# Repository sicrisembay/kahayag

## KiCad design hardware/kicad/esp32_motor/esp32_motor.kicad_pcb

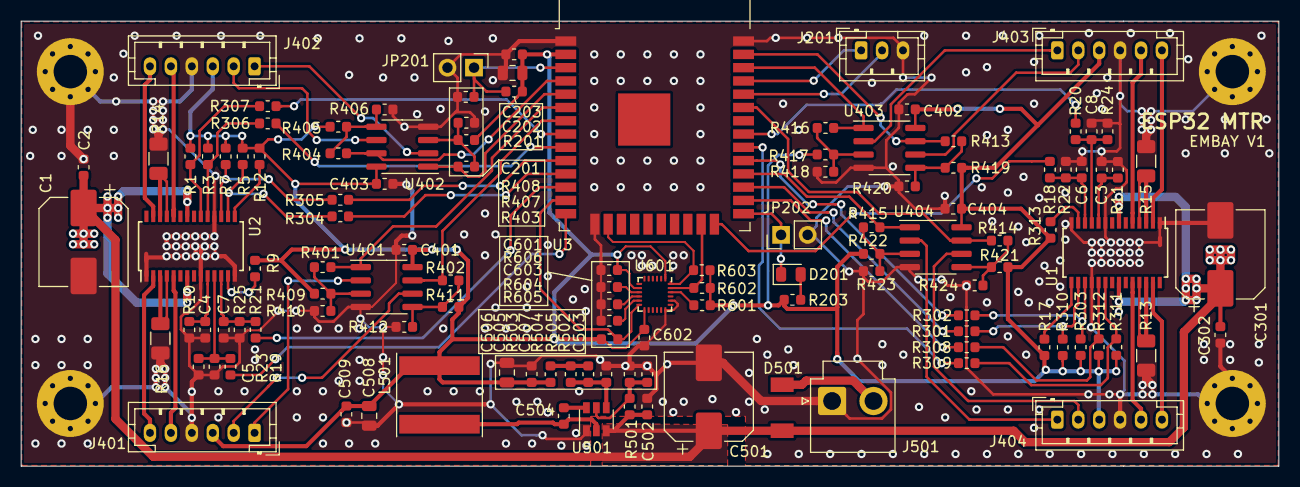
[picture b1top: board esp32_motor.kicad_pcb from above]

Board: 2 copper layers, 120.3 x 42.5 mm, 124 parts (0 on the bottom side), 87 nets.

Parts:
C1, C301, C501: 100uF; CP_Elec_8x10
C2, C5, C6, C7, C8, C201, C203, C302, C401, C402, C403, C404, C504, C505, C509, C602, C603: 0.1uF; C_0603_1608Metric
C3, C4: 470pF; C_0603_1608Metric
C202, C506, C508: 22uF; C_0805_2012Metric
C502: 1uF; C_0603_1608Metric
C503: DNP; C_0603_1608Metric
C507: 75pF; C_0603_1608Metric
C601: 10nF; C_0603_1608Metric
D201: LED; LED_0805_2012Metric
D501: SK14; SOD-128
H701, H702, H703, H704: MountingHole_Pad; MountingHole_3.2mm_M3_Pad_Via
J201: Program; JST_PH_B3B-PH-K_1x03_P2.00mm_Vertical
J401: MOTOR1; JST_PH_B6B-PH-K_1x06_P2.00mm_Vertical
J402: MOTOR2; JST_PH_B6B-PH-K_1x06_P2.00mm_Vertical
J403: MOTOR3; JST_PH_B6B-PH-K_1x06_P2.00mm_Vertical
J404: MOTOR4; JST_PH_B6B-PH-K_1x06_P2.00mm_Vertical
J501: 24V_IN; JST_VH_B2P-VH-B_1x02_P3.96mm_Vertical
JP201: RESET; PinHeader_1x02_P2.54mm_Vertical
JP202: MODE; PinHeader_1x02_P2.54mm_Vertical
L501: 10uH; L_Taiyo-Yuden_NR-80xx
R1, R3, R5, R7, R9, R12, R17, R201, R303, R310, R311, R312, R313, R405, R406, R407, R408, R409, R410, R411, R412, R417, R418, R419, R420, R421, R422, R423, R424, R601, R604, R605, R606: 10K; R_0603_1608Metric
R10, R11: 82K; R_0603_1608Metric
R13, R14, R15, R16: 0.1; R_1206_3216Metric
R18, R19, R20, R21, R602, R603: 4.7K; R_0603_1608Metric
R22, R23, R24, R25: 5K; R_0603_1608Metric
R203: 220R; R_0603_1608Metric
R301, R302, R304, R305, R306, R307, R308, R309: 200; R_0603_1608Metric
R401, R402, R403, R404, R413, R414, R415, R416: 50K; R_0603_1608Metric
R501: 511K; R_0603_1608Metric
R502, R504: 100K; R_0603_1608Metric
R503: 49.9R; R_0603_1608Metric
R505: 22K; R_0603_1608Metric
U1, U2: BD62220AEFV; HTSSOP-28-BD62220AEFV
U3: ESP32-WROOM-32D; ESP32-WROOM-32
U401, U402, U403, U404: LM393; SOIC-8_3.9x4.9mm_P1.27mm
U501: TPS54302; SOT-23-6
U601: MPU-9250; InvenSense_QFN-24_3x3mm_P0.4mm

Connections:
3V3_OUT: C202.1, C203.1, C401.1, C402.1, C403.1, C404.1, C505.2, C506.2, C508.2, C509.2, C601.1, C602.1, J401.3, J402.3, J403.3, J404.3, L501.2, R1.1, R3.1, R5.1, R7.1, R9.1, R12.1, R17.1, R201.1, R203.1, R303.1, R310.1, R311.1, R312.1, R313.1, R405.1, R407.1, R409.1, R411.1, R417.1, R419.1, R421.1, R422.1, R503.1, R601.1, R602.1, R603.1, R605.1, U3.2, U401.8, U402.8, U403.8, U404.8, U601.1, U601.8, U601.13
24VDC: C1.1, C2.1, C301.1, C302.1, C501.1, C502.1, D501.1, R501.1, U1.7, U1.22, U2.7, U2.22, U501.3
/motor_drive/M1_VREF: C5.1, R19.1, R23.1, U2.11
/motor_drive/M2_VREF: C7.1, R21.1, R25.1, U2.12
/motor_drive/M3_VREF: C8.1, R20.1, R24.1, U1.11
/motor_drive/M4_VREF: C6.1, R18.1, R22.1, U1.12
GND: C1.2, C2.2, C3.2, C4.2, C5.2, C6.2, C7.2, C8.2, C201.2, C202.2, C203.2, C301.2, C302.2, C401.2, C402.2, C403.2, C404.2, C501.2, C502.2, C503.2, C505.1, C506.1, C508.1, C509.1, C601.2, C602.2, C603.1, H701.1, H702.1, H703.1, H704.1, J201.3, J401.4, J402.4, J403.4, J404.4, J501.1, JP201.2, JP202.2, R10.2, R11.2, R13.2, R14.2, R15.2, R16.2, R22.2, R23.2, R24.2, R25.2, R406.1, R408.1, R410.1, R412.1, R418.1, R420.1, R423.1, R424.1, R502.2, R505.2, R604.2, R606.2, U1.1, U1.9, U1.14, U1.18, U1.29, U2.1, U2.9, U2.14, U2.18, U2.29, U3.1, U3.15, U3.38, U401.4, U402.4, U403.4, U404.4, U501.1, U601.18, U601.20
I2C_SCL: R602.2, U3.23, U601.23
I2C_SDA: R603.2, U3.16, U601.24
MOT1A_OUT: J401.5, U2.5
MOT1B_OUT: J401.6, U2.2
MOT1_ENCA: R401.2, U3.6, U401.1
MOT1_ENCB: R402.2, U3.7, U401.7
MOT1_INA: R304.2, U3.11
MOT1_INB: R305.1, U3.10
MOT1_VREF: R19.2, U3.14
MOT2A_OUT: J402.5, U2.24
MOT2B_OUT: J402.6, U2.27
MOT2_ENCA: R403.2, U3.5, U402.1
MOT2_ENCB: R404.2, U3.4, U402.7
MOT2_INA: R306.2, U3.9
MOT2_INB: R307.1, U3.8
MOT2_VREF: R21.2, U3.12
MOT3A_OUT: J403.5, U1.5
MOT3B_OUT: J403.6, U1.2
MOT3_ENCA: R416.2, U3.36, U403.1
MOT3_ENCB: R413.2, U3.37, U403.7
MOT3_INA: R301.2, U3.27
MOT3_INB: R302.1, U3.29
MOT3_VREF: R20.2, U3.31
MOT4A_OUT: J404.5, U1.24
MOT4B_OUT: J404.6, U1.27
MOT4_ENCA: R415.2, U3.28, U404.1
MOT4_ENCB: R414.2, U3.33, U404.7
MOT4_INA: R308.2, U3.26
MOT4_INB: R309.1, U3.30
MOT4_VREF: R18.2, U3.24
MPU_9250_INT: R605.2, U3.13, U601.12
unnamed: C3.1, R11.1, U1.10
unnamed: C4.1, R10.1, U2.10
unnamed: C201.1, JP201.1, R201.2, U3.3
unnamed: C503.1, R501.2, R502.1, U501.5
unnamed: C504.1, L501.1, U501.2
unnamed: C504.2, U501.6
unnamed: C507.1, R504.2, R505.1, U501.4
unnamed: C507.2, R503.2, R504.1
unnamed: C603.2, U601.10
unnamed: D201.1, JP202.1, U3.25
unnamed: D201.2, R203.2
unnamed: D501.2, J501.2
unnamed: J201.1, U3.35
unnamed: J201.2, U3.34
unnamed: J401.1, U401.2
unnamed: J401.2, U401.6
unnamed: J402.1, U402.2
unnamed: J402.2, U402.6
unnamed: J403.1, U403.2
unnamed: J403.2, U403.6
unnamed: J404.1, U404.2
unnamed: J404.2, U404.6
unnamed: R1.2, R307.2, U2.20
unnamed: R3.2, R306.1, U2.19
unnamed: R9.2, U2.13
unnamed: R12.2, U2.15
unnamed: R13.1, U1.25, U1.26
unnamed: R14.1, U2.25, U2.26
unnamed: R15.1, U1.3, U1.4
unnamed: R16.1, U2.3, U2.4
unnamed: R17.2, U1.15
unnamed: R301.1, R310.2, U1.16
unnamed: R302.2, R303.2, U1.17
unnamed: R5.2, R304.1, U2.16
unnamed: R7.2, R305.2, U2.17
unnamed: R308.1, R312.2, U1.19
unnamed: R309.2, R311.2, U1.20
unnamed: R313.2, U1.13
unnamed: R401.1, R409.2, R410.2, U401.3
unnamed: R402.1, R411.2, R412.2, U401.5
unnamed: R403.1, R407.2, R408.2, U402.3
unnamed: R404.1, R405.2, R406.2, U402.5
unnamed: R413.1, R419.2, R420.2, U403.5
unnamed: R414.1, R421.2, R424.2, U404.5
unnamed: R415.1, R422.2, R423.2, U404.3
unnamed: R416.1, R417.2, R418.2, U403.3
unnamed: R601.2, U601.22
unnamed: R604.1, U601.11
unnamed: R606.1, U601.9

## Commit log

2019-05-18 Added ESP-MDF as submodule
2019-05-18 Added qpc as submodule
2019-05-18 Added project
2019-05-18 Added project settings for Eclipse. Added placeholder for System Management Active Object.
2019-05-20 Added InputOutput component. Increased stack size of Active Objects.
2019-05-20 Added boot check state machine in SysMngt component Updated InOut component
2019-05-26 + Updated qpc submodule (fixed qpc esp32 port hard fault) + Added Wifi component in System Management + Added Provision component in System Management + Added worker task to handle blocking calls + U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
2019-05-29 first attempt for Provision service implementation
2019-06-01 Implemented Provisioning for Wifi credential.
2019-06-07 Updated Wifi SM
2019-06-07 new motor control project
2019-06-09 Added quadrature encoder and initial bdc motor active object
2019-06-12 first commit on board design
2019-06-13 implemented motor driver
2019-06-16 PCB v1
2019-06-18 Updated PCB Layout. This is PCB release candidate 1
2019-06-20 PCB Release v1
2019-06-28 pulled qpc submodule
2019-06-30 + Fixed encoder bug that resulted to a divide-by-zero hardfault + Added support for constant current operation in motor_driver + Updated bdcMotorCtrl IO configuration + Added configuration for BD6222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
2019-07-02 Pulled bug fixes on libfixmath
2019-07-05 + Implemented Speed control Loop of BDC motor + Implemented PID controller + Updated encoder API + Fixed motor driver PWM resolution + Updated motor drive direction + Updated LibFixMath Config (disab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
2019-07-08 + initial MPU9250 support + initial implementation of position control
2019-07-12 + Added tuning tool + updated bdcMotor API's + updated bdcMotor/encoder API's + updated user commands
2019-07-19 + Updated motor driver (support 40kHz and 80kHz) + Updated default motor control coefficients + Imported core files from Invensense Embedded Motion Driver 6.12
2019-08-06 + updated ESP_MOTOR board + updated mpu9250 driver
